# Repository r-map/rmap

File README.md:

Description

software to collect weather data contributed by citizens; to make
these data available for weather services and homeland security; to
provide feedback to the data contributors so that they have the tools
to check and improve their data quality

Stima open source hardware datalogger

RMAP server software

http://doc.rmap.cc

http://rmap.cc

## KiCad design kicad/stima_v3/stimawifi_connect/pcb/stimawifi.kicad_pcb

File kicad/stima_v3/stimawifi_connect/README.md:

# STiMA WiFi Compact pcb base

Kicad project for a compat pcb useful for a portable monitoring station.

Directory tree structure inspired by https://github.com/sdp8483/kicad_dir_structure/tree/master
github repository based on Hackaday article: https://hackaday.com/2017/05/18/kicad-best-practises-library-management/

## Directory structure

 - __./pcb__        Kicad files
 - __./mechanical__ 3d printing related files

 - __./pcb/pcb_render__ Board 3d renderings
 - __./pcb_3d_models__  Kicad 3d models needed for rendering
 - __./pcb/images__  Images for Silk screen
 - __./pcb/lib_fp__   Local Footprints libraries
 - __./pcb/lib_sch__  Local Symbols libraries

## Related project

https://github.com/r-map/rmap

It is a software aimed to 
 - collect air quality data contributed by citizens; 
 - make collected data available for weather services and homeland security; 
 - provide feedback to the data contributors for educational purpose.

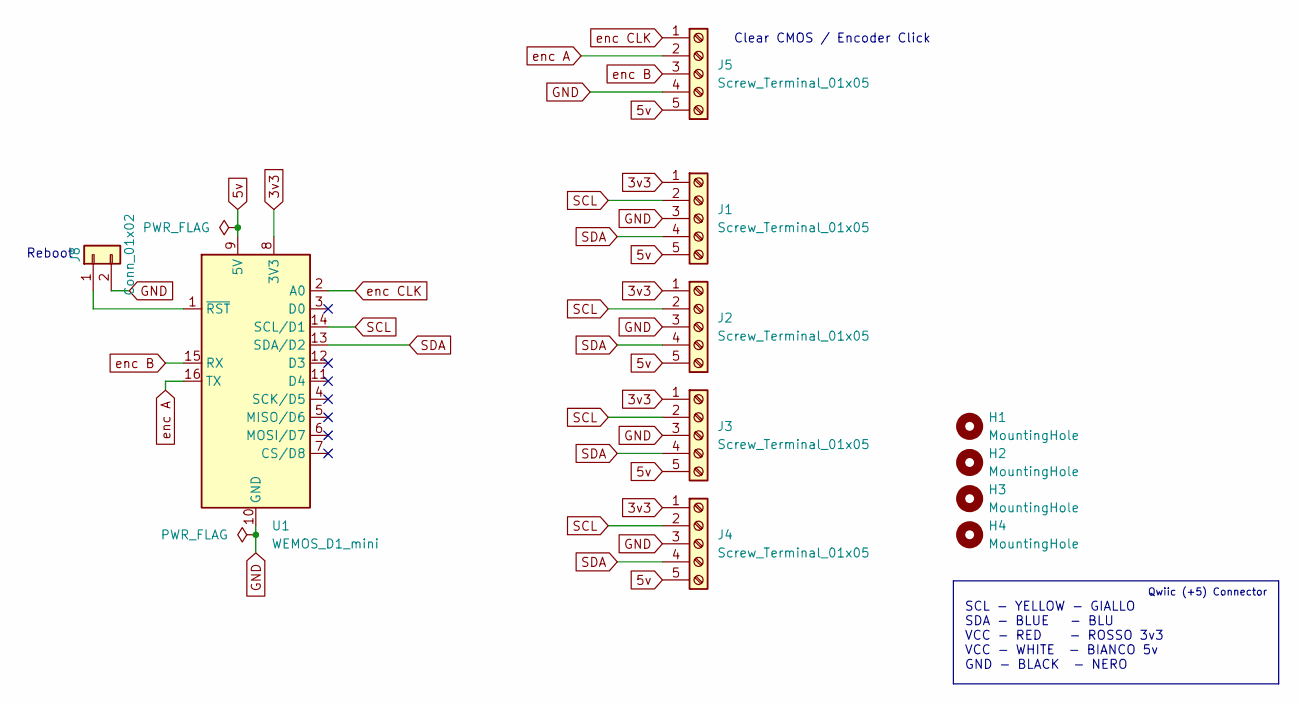
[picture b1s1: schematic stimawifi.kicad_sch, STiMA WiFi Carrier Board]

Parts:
H1, H2, H3, H4: MountingHole; MountingHole_3.2mm_M3
J1, J2, J3, J4, J5: Screw_Terminal_01x05; TerminalBlock_Xinya_XY308-2.54-5P_1x05_P2.54mm_Horizontal
J8: Conn_01x02; PinHeader_1x02_P2.54mm_Vertical
U1: WEMOS_D1_mini; WEMOS_D1_mini_light

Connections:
3v3: J1.1, J2.1, J3.1, J4.1, U1.8 (3V3)
5v: J1.5, J2.5, J3.5, J4.5, J5.5, U1.9 (5V)
GND: J1.3, J2.3, J3.3, J4.3, J5.4, J8.2, U1.10 (GND)
unnamed: J8.1, U1.1 (~RST)
SCL: J1.2, J2.2, J3.2, J4.2, U1.14 (SCL/D1)
SDA: J1.4, J2.4, J3.4, J4.4, U1.13 (SDA/D2)
enc A: J5.2, U1.16 (TX)
enc B: J5.3, U1.15 (RX)
enc CLK: J5.1, U1.2 (A0)

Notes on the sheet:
Clear CMOS / Encoder Click
SCL - YELLOW - GIALLO SDA - BLUE - BLU VCC - RED - ROSSO 3v3 VCC - WHITE - BIANCO 5v GND - BLACK - NERO
Qwiic (+5) Connector
Reboot

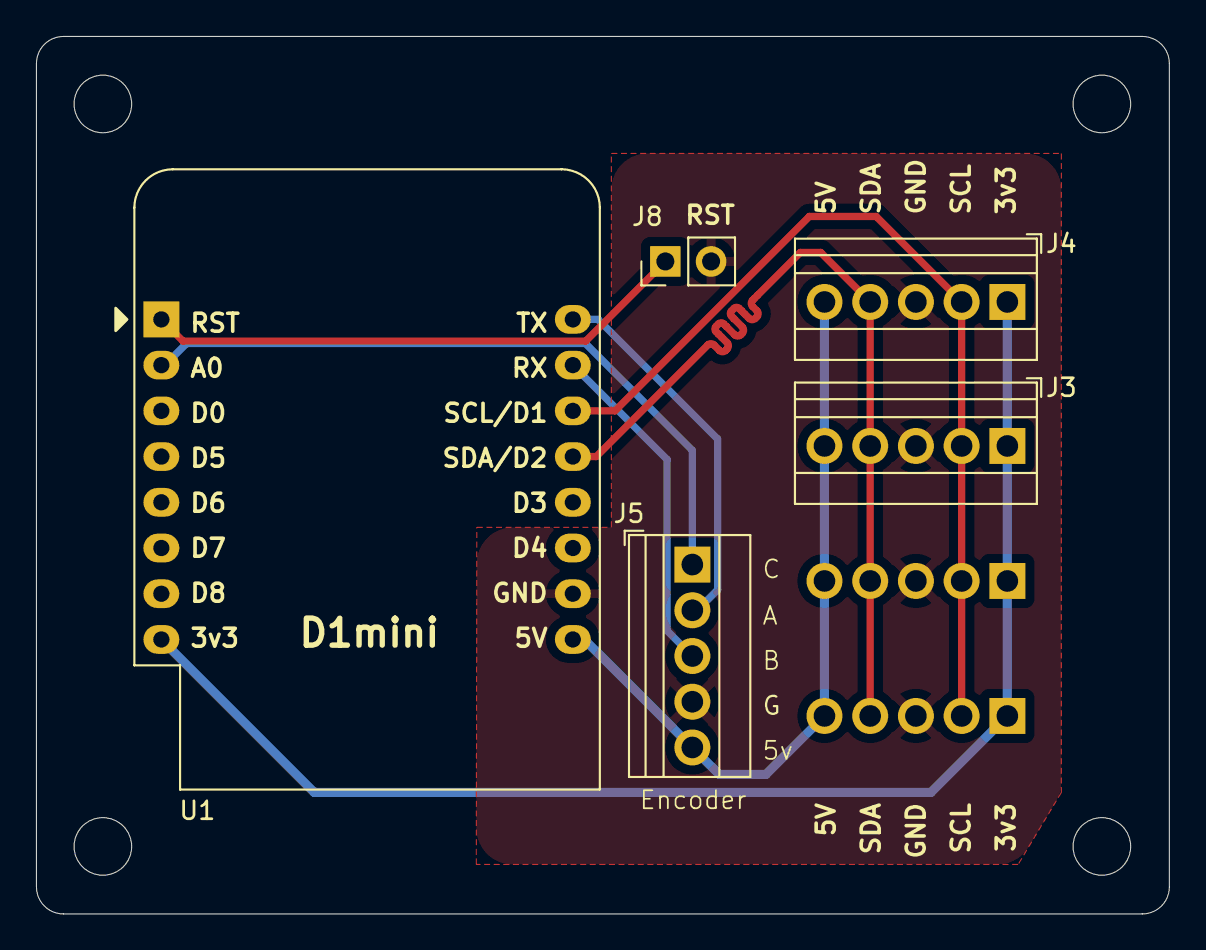
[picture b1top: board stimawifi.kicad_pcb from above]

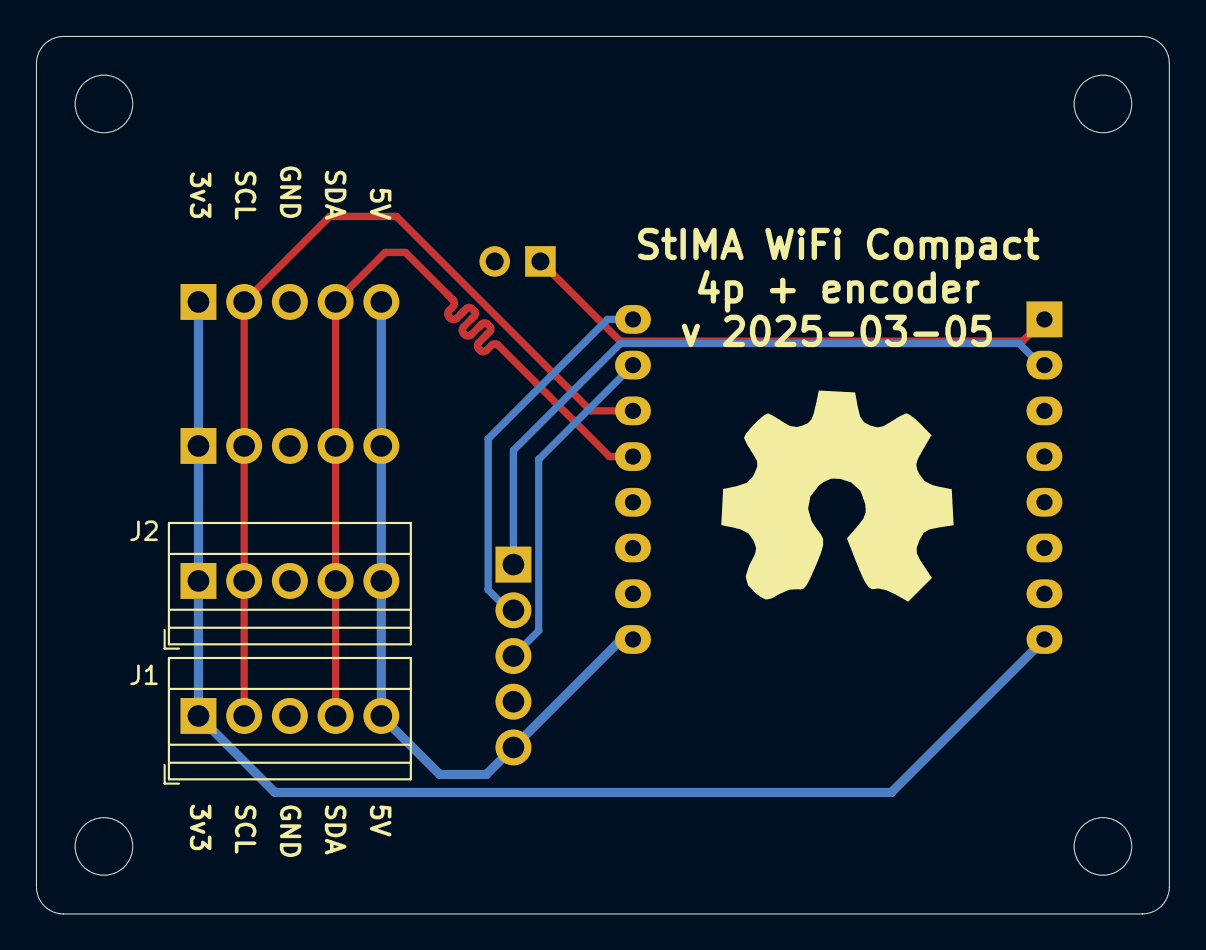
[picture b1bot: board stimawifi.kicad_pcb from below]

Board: 2 copper layers, 62.9 x 48.8 mm, 12 parts (3 on the bottom side), 9 nets.

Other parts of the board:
Open Hardvare Logo: LOGO; ohlogo

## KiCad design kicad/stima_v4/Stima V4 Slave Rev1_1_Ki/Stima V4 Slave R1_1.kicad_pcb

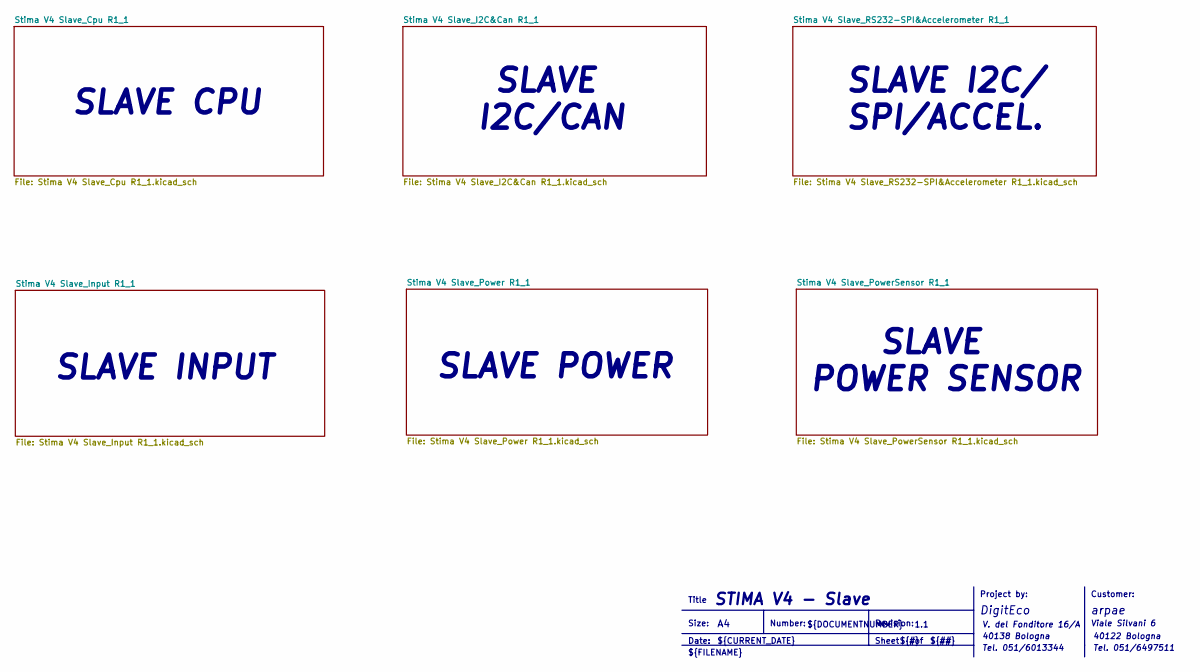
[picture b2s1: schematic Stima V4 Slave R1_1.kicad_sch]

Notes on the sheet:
Tel. 051/6013344
1.1
SLAVE CPU
Project by:
${#}
${TITLE}
${CURRENT_DATE}
Viale Silvani 6
DigitEco
${FILENAME}
SLAVE POWER SENSOR
${##}
${DOCUMENTNUMBER}
STIMA V4 - Slave
Size:
Number:
SLAVE I2C/CAN
Sheet
V. del Fonditore 16/A
Customer:
arpae
40138 Bologna
Date:
Title
Revision:
Tel. 051/6497511
SLAVE POWER
SLAVE INPUT
SLAVE I2C/ SPI/ACCEL.
40122 Bologna

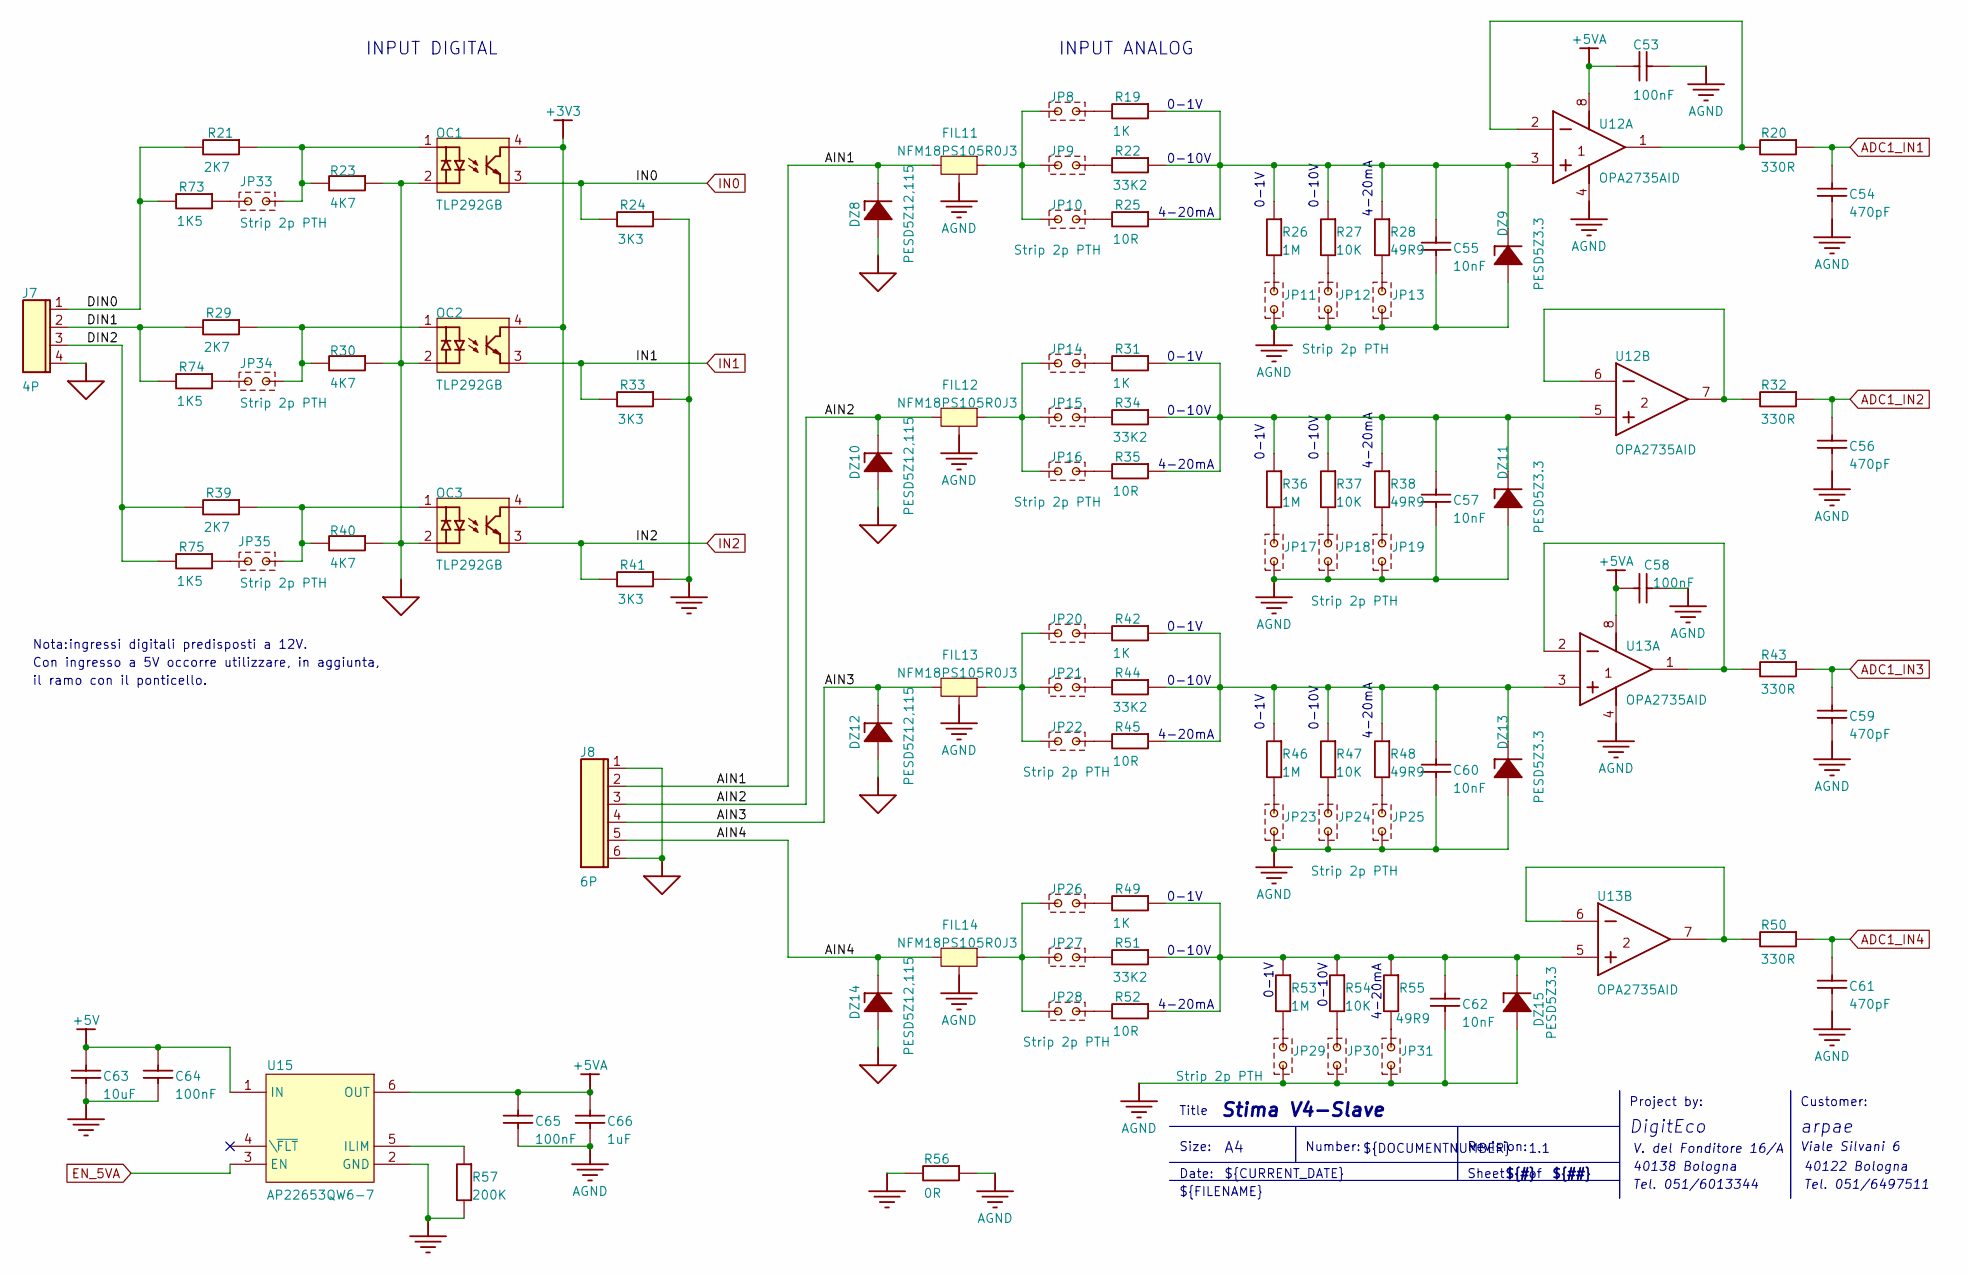
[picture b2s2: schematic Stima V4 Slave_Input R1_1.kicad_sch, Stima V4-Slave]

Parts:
C53, C58, C64, C65: 100nF; 0603; VOLTAGE 50V
C54, C56, C59, C61: 470pF; 0603; VOLTAGE 50V
C55, C57, C60, C62: 10nF; 0603; VOLTAGE 50V
C63: 10uF; 0603; VOLTAGE 20V
C66: 1uF; 0603; VOLTAGE 20V
DZ8, DZ10, DZ12, DZ14: PESD5Z12,115; SOD 523(SC-79)
DZ9, DZ11, DZ13, DZ15: PESD5Z3.3; SOD 523(SC-79)
FIL11, FIL12, FIL13, FIL14: NFM18PS105R0J3; NFM18PS
J7: 4P; CONN_4P-P381
J8: 6P; CONN_6P-P381
JP8, JP9, JP10, JP11, JP12, JP13, JP14, JP15, JP16, JP17, JP18, JP19, JP20, JP21, JP22, JP23, JP24, JP25, JP26, JP27, JP28, JP29, JP30, JP31, JP33, JP34, JP35: Strip 2p PTH; STRIP2P
OC1, OC2, OC3: TLP292GB; SO4-OPTO
R19, R31, R42, R49: 1K; 0603
R20, R32, R43, R50: 330R; 0603
R21, R29, R39: 2K7; 0805
R22, R34, R44, R51: 33K2; 0603
R23, R30, R40: 4K7; 0603
R24, R33, R41: 3K3; 0603
R25, R35, R45, R52: 10R; 0603
R26, R36, R46, R53: 1M; 0603
R27, R37, R47, R54: 10K; 0603
R28, R38, R48, R55: 49R9; 0603
R56: 0R; 0603
R57: 200K; 0603
R73, R74, R75: 1K5; 0805
U12, U13: OPA2735AID; SO8
U15: AP22653QW6-7; SOT26

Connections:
+3V3: OC1.4, OC2.4, OC3.4; also elsewhere on the board
+5V: C63.1, C64.1, U15.1 (IN); also elsewhere on the board
+5VA: C53.1, C58.1, C65.1, C66.1, U12.8 (V+), U13.8 (V+), U15.6 (OUT)
/Stima V4 Slave_Input R1_1/AIN1: DZ8.1 (K), FIL11.1 (I), J8.2
/Stima V4 Slave_Input R1_1/AIN2: DZ10.1 (K), FIL12.1 (I), J8.3
/Stima V4 Slave_Input R1_1/AIN3: DZ12.1 (K), FIL13.1 (I), J8.4
/Stima V4 Slave_Input R1_1/AIN4: DZ14.1 (K), FIL14.1 (I), J8.5
/Stima V4 Slave_Input R1_1/DIN0: J7.1, R21.1, R73.1
/Stima V4 Slave_Input R1_1/DIN1: J7.2, R29.1, R74.1
/Stima V4 Slave_Input R1_1/DIN2: J7.3, R39.1, R75.1
ADC1_IN1: C54.1, R20.2; also elsewhere on the board
ADC1_IN2: C56.1, R32.2; also elsewhere on the board
ADC1_IN3: C59.1, R43.2; also elsewhere on the board
ADC1_IN4: C61.1, R50.2; also elsewhere on the board
AGND: C53.2, C54.2, C55.2, C56.2, C57.2, C58.2, C59.2, C60.2, C61.2, C62.2, C65.2, C66.2, DZ9.2 (A), DZ11.2 (A), DZ13.2 (A), DZ15.2 (A), FIL11.3 (M), FIL12.3 (M), FIL13.3 (M), FIL14.3 (M), JP11.1, JP12.1, JP13.1, JP17.1, JP18.1, JP19.1, JP23.1, JP24.1, JP25.1, JP29.1, JP30.1, JP31.1, R56.2, U12.4 (V-), U13.4 (V-); also elsewhere on the board
EGND: DZ8.2 (A), DZ10.2 (A), DZ12.2 (A), DZ14.2 (A), J7.4, J8.1, J8.6, OC1.2, OC2.2, OC3.2, R23.2, R30.2, R40.2; also elsewhere on the board
EN_5VA: U15.3 (EN); also elsewhere on the board
GND: C63.2, C64.2, R24.2, R33.2, R41.2, R56.1, R57.2, U15.2 (GND); also elsewhere on the board
IN0: OC1.3, R24.1; also elsewhere on the board
IN1: OC2.3, R33.1; also elsewhere on the board
IN2: OC3.3, R41.1; also elsewhere on the board
unnamed: C55.1, DZ9.1 (K), R19.2, R22.2, R25.2, R26.2, R27.2, R28.2, U12.3 (IN+)
unnamed: C57.1, DZ11.1 (K), R31.2, R34.2, R35.2, R36.2, R37.2, R38.2, U12.5 (IN+)
unnamed: C60.1, DZ13.1 (K), R42.2, R44.2, R45.2, R46.2, R47.2, R48.2, U13.3 (IN+)
unnamed: C62.1, DZ15.1 (K), R49.2, R51.2, R52.2, R53.2, R54.2, R55.2, U13.5 (IN+)
unnamed: FIL11.2 (O), JP8.1, JP9.1, JP10.1
unnamed: FIL12.2 (O), JP14.1, JP15.1, JP16.1
unnamed: FIL13.2 (O), JP20.1, JP21.1, JP22.1
unnamed: FIL14.2 (O), JP26.1, JP27.1, JP28.1
unnamed: JP8.2, R19.1
unnamed: JP9.2, R22.1
unnamed: JP10.2, R25.1
unnamed: JP11.2, R26.1
unnamed: JP12.2, R27.1
unnamed: JP13.2, R28.1
unnamed: JP14.2, R31.1
unnamed: JP15.2, R34.1
unnamed: JP16.2, R35.1
unnamed: JP17.2, R36.1
unnamed: JP18.2, R37.1
unnamed: JP19.2, R38.1
unnamed: JP20.2, R42.1
unnamed: JP21.2, R44.1
unnamed: JP22.2, R45.1
unnamed: JP23.2, R46.1
unnamed: JP24.2, R47.1
unnamed: JP25.2, R48.1
unnamed: JP26.2, R49.1
unnamed: JP27.2, R51.1
unnamed: JP28.2, R52.1
unnamed: JP29.2, R53.1
unnamed: JP30.2, R54.1
unnamed: JP31.2, R55.1
unnamed: JP33.1, R73.2
unnamed: JP33.2, OC1.1, R21.2, R23.1
unnamed: JP34.1, R74.2
unnamed: JP34.2, OC2.1, R29.2, R30.1
unnamed: JP35.1, R75.2
unnamed: JP35.2, OC3.1, R39.2, R40.1
unnamed: R20.1, U12.1 (OUT), U12.2 (IN-)
unnamed: R32.1, U12.6 (IN-), U12.7 (OUT)
unnamed: R43.1, U13.1 (OUT), U13.2 (IN-)
unnamed: R50.1, U13.6 (IN-), U13.7 (OUT)
unnamed: R57.1, U15.5 (ILIM)

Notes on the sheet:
INPUT DIGITAL
0-1V
${FILENAME}
ingressi digitali predisposti a 12V.
Title
arpae
Tel. 051/6013344
0-10V
${TITLE}
Number:
Sheet
Viale Silvani 6
40138 Bologna
4-20mA
il ramo con il ponticello.
Customer:
${CURRENT_DATE}
40122 Bologna
Tel. 051/6497511
Date:
Size:
${#}
INPUT ANALOG
1.1
${##}
Nota:
Revision:
DigitEco
${DOCUMENTNUMBER}
V. del Fonditore 16/A
Con ingresso a 5V occorre utilizzare, in aggiunta,
Project by:

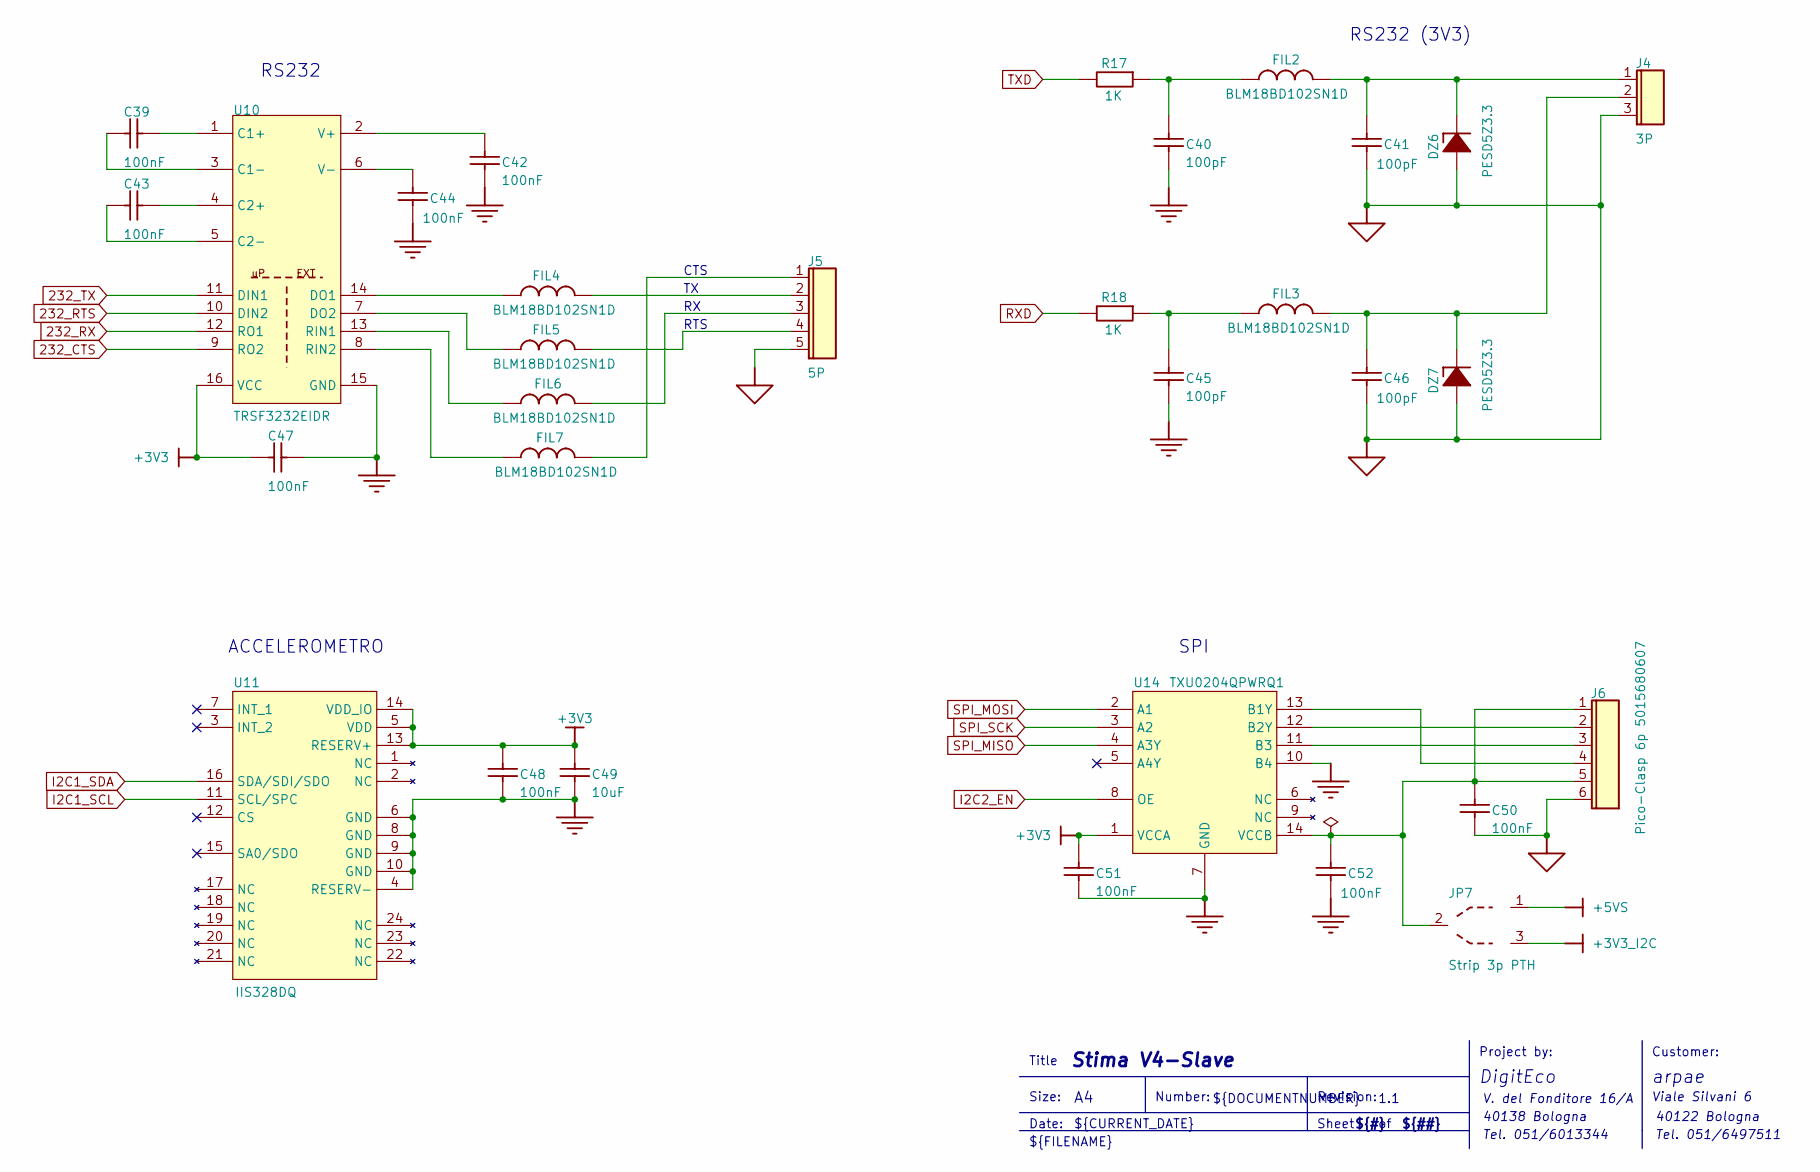
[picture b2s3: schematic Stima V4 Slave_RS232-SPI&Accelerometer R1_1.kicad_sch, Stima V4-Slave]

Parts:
C39, C42, C43, C44, C47, C48, C50, C51, C52: 100nF; 0603; VOLTAGE 50V
C40, C41, C45, C46: 100pF; 0603; VOLTAGE 50V
C49: 10uF; 0603; VOLTAGE 16V
DZ6, DZ7: PESD5Z3.3; SOD 523(SC-79)
FIL2, FIL3, FIL4, FIL5, FIL6, FIL7: BLM18BD102SN1D; 0603
J4: 3P; CONN_3P-P381
J5: 5P; CONN_5P-P381
J6: Pico-Clasp 6p 5015680607; PICOCLASP6P_REV-MIO
JP7: Strip 3p PTH; STRIP3PP254
R17, R18: 1K; 0603
U10: TRSF3232EIDR; SO16
U11: IIS328DQ; VQFN24
U14: TXU0204QPWRQ1; TSSOP14

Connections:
232_CTS: U10.9 (RO2); also elsewhere on the board
232_RTS: U10.10 (DIN2); also elsewhere on the board
232_RX: U10.12 (RO1); also elsewhere on the board
232_TX: U10.11 (DIN1); also elsewhere on the board
+3V3: C47.1, C48.1, C49.1, C51.1, U10.16 (VCC), U11.5 (VDD), U11.13 (RESERV+), U11.14 (VDD_IO), U14.1 (VCCA); also elsewhere on the board
+3V3_I2C: JP7.3; also elsewhere on the board
+5VS: JP7.1; also elsewhere on the board
EGND: C41.1, C46.1, C50.2, DZ6.2 (A), DZ7.2 (A), J4.3, J5.5, J6.6; also elsewhere on the board
GND: C40.1, C42.1, C44.1, C45.1, C47.2, C48.2, C49.2, C51.2, C52.2, U10.15 (GND), U11.4 (RESERV-), U11.6 (GND), U11.8 (GND), U11.9 (GND), U11.10 (GND), U14.7 (GND), U14.10 (B4); also elsewhere on the board
I2C1_SCL: U11.11 (SCL/SPC); also elsewhere on the board
I2C1_SDA: U11.16 (SDA/SDI/SDO); also elsewhere on the board
I2C2_EN: U14.8 (OE); also elsewhere on the board
unnamed: C40.2, FIL2.1, R17.2
unnamed: C45.2, FIL3.1, R18.2
unnamed: C41.2, DZ6.1 (K), FIL2.2, J4.1
unnamed: C46.2, DZ7.1 (K), FIL3.2, J4.2
unnamed: FIL4.2, J5.2
unnamed: FIL5.2, J5.4
unnamed: FIL6.2, J5.3
unnamed: FIL7.2, J5.1
unnamed: C39.2, U10.1 (C1+)
unnamed: C39.1, U10.3 (C1-)
unnamed: C43.2, U10.4 (C2+)
unnamed: C43.1, U10.5 (C2-)
unnamed: FIL4.1, U10.14 (DO1)
unnamed: FIL5.1, U10.7 (DO2)
unnamed: FIL6.1, U10.13 (RIN1)
unnamed: FIL7.1, U10.8 (RIN2)
unnamed: C42.2, U10.2 (V+)
unnamed: C44.2, U10.6 (V-)
unnamed: J6.4, U14.13 (B1Y)
unnamed: J6.2, U14.12 (B2Y)
unnamed: J6.3, U14.11 (B3)
unnamed: C50.1, C52.1, J6.1, J6.5, JP7.2, U14.14 (VCCB)
RXD: R18.1; also elsewhere on the board
SPI_MISO: U14.4 (A3Y); also elsewhere on the board
SPI_MOSI: U14.2 (A1); also elsewhere on the board
SPI_SCK: U14.3 (A2); also elsewhere on the board
TXD: R17.1; also elsewhere on the board

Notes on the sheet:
ACCELEROMETRO
V. del Fonditore 16/A
${CURRENT_DATE}
RTS
Sheet
Revision:
${TITLE}
RS232 (3V3)
Customer:
arpae
Viale Silvani 6
40122 Bologna
${#}
Tel. 051/6497511
Date:
1.1
CTS
RS232
${##}
Number:
${DOCUMENTNUMBER}
40138 Bologna
${FILENAME}
Size:
Project by:
Title
Tel. 051/6013344
SPI
DigitEco

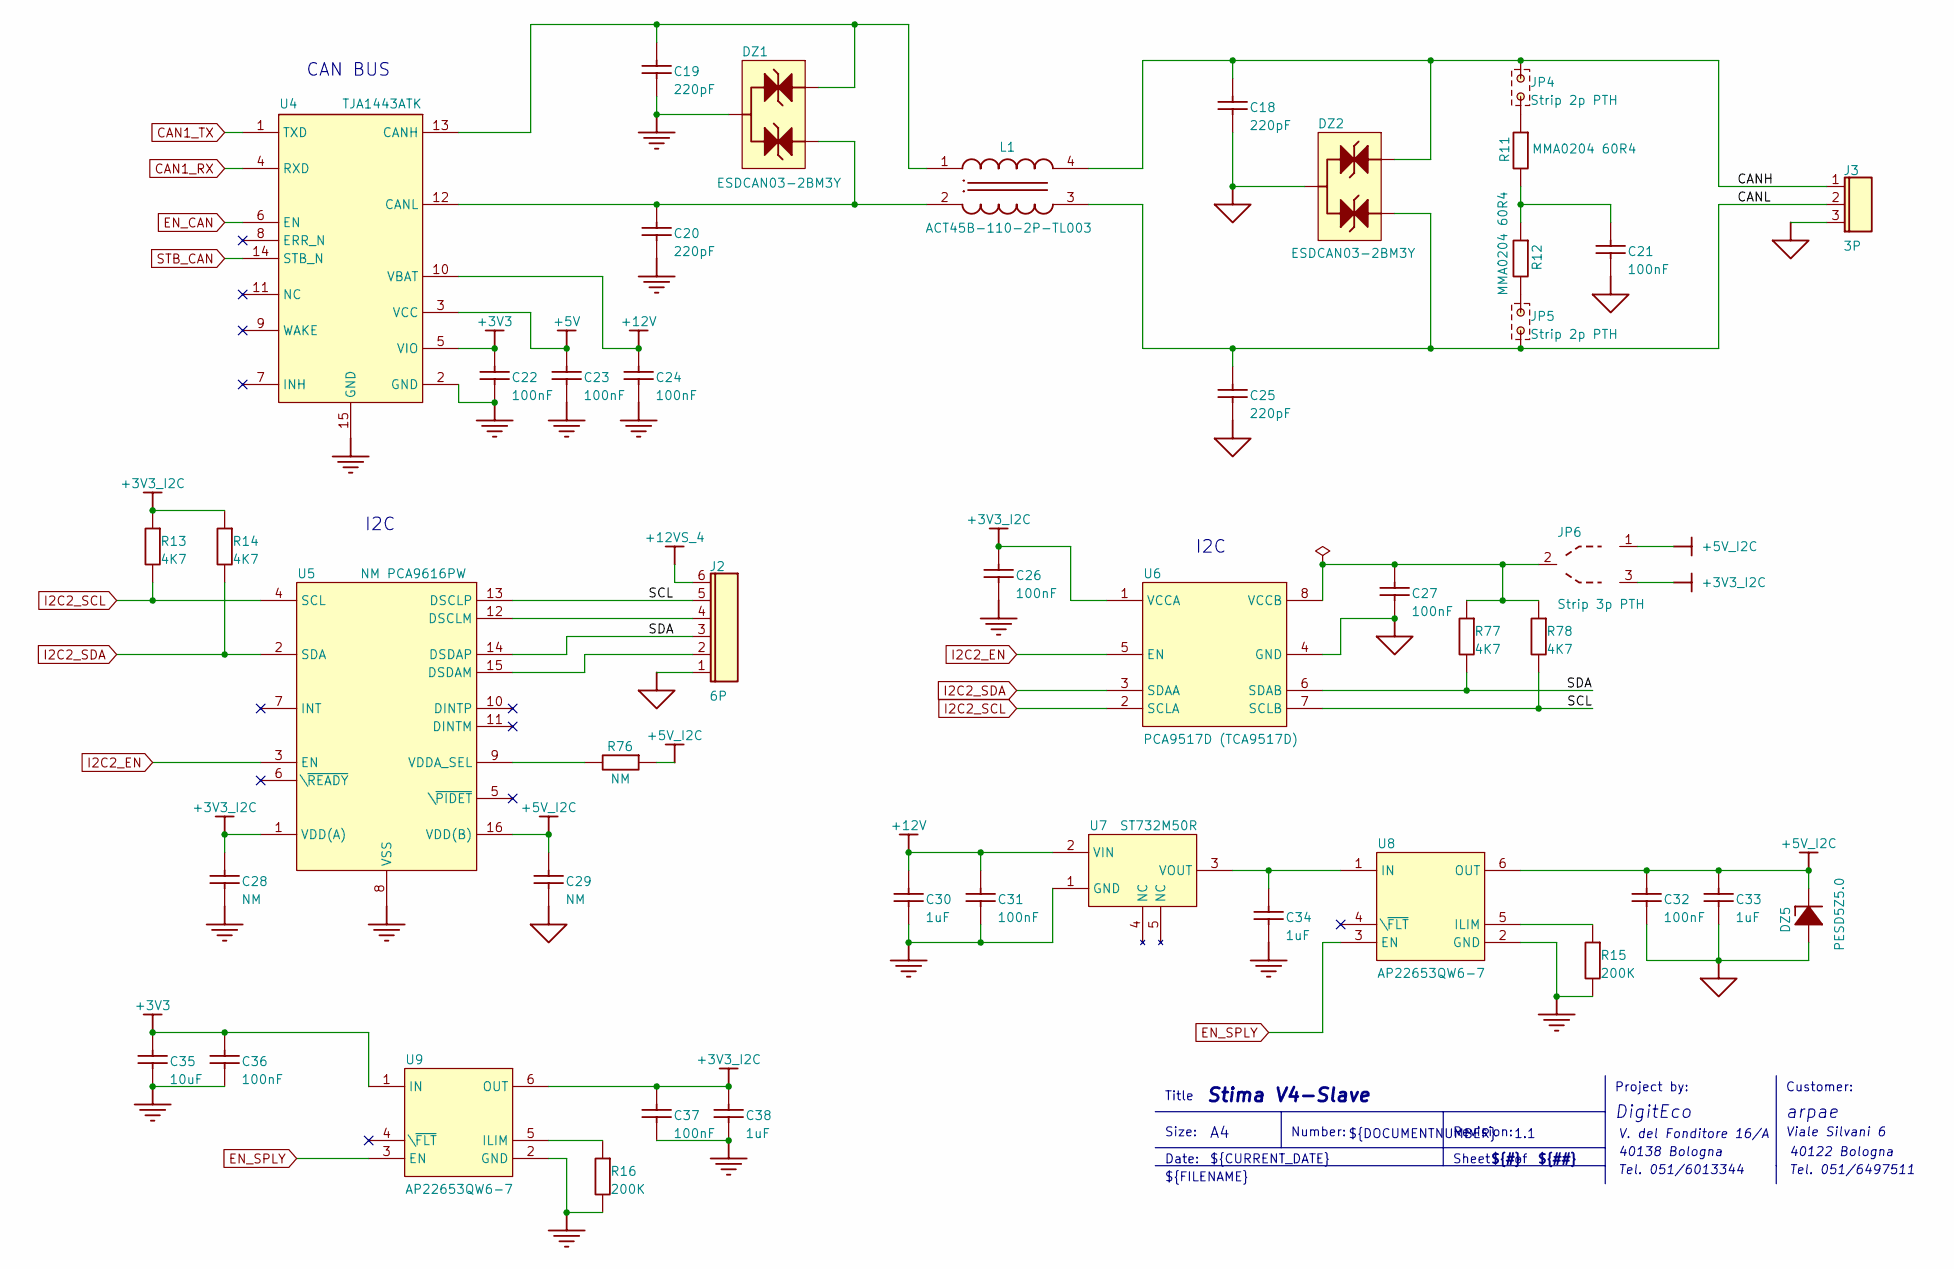
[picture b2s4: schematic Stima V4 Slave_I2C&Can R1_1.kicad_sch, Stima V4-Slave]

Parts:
C18, C19, C20, C25: 220pF; 0603; VOLTAGE 50V
C21, C22, C23, C24, C26, C27, C31, C32, C36, C37: 100nF; 0603; VOLTAGE 50V
C28, C29: NM; 0603; VOLTAGE 50V
C30, C33, C34, C38: 1uF; 0603; VOLTAGE 20V
C35: 10uF; 0603; VOLTAGE 20V
DZ1, DZ2: ESDCAN03-2BM3Y; QFN-3L-DFN1110
DZ5: PESD5Z5.0; SOD 523(SC-79)
J2: 6P; CONN_6P-P381
J3: 3P; CONN_3P-P381
JP4, JP5: Strip 2p PTH; STRIP2P
JP6: Strip 3p PTH; STRIP3PP254
L1: ACT45B-110-2P-TL003; ACT45B TDK-MIO
R11, R12: MMA0204 60R4; MELFRESMMA0204
R13, R14, R77, R78: 4K7; 0603
R15, R16: 200K; 0603
R76: NM; 0603
U4: TJA1443ATK; HVSON14
U5: NM PCA9616PW; TSSOP16
U6: PCA9517D (TCA9517D); SO8
U7: ST732M50R; SOT23_5
U8, U9: AP22653QW6-7; SOT26

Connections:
+3V3: C22.1, C35.1, C36.1, U4.5 (VIO), U9.1 (IN); also elsewhere on the board
+3V3_I2C: C26.1, C28.1, C37.1, C38.1, JP6.3, R13.2, R14.2, U5.1 (VDD(A)), U6.1 (VCCA), U9.6 (OUT); also elsewhere on the board
+5V: C23.1, U4.3 (VCC); also elsewhere on the board
+5V_I2C: C29.1, C32.1, C33.1, DZ5.1 (K), JP6.1, R76.1, U5.16 (VDD(B)), U8.6 (OUT)
+12V: C24.2, C30.1, C31.1, U4.10 (VBAT), U7.2 (VIN); also elsewhere on the board
+12VS_4: J2.6; also elsewhere on the board
/Stima V4 Slave_I2C&Can R1_1/CANH: C18.2, DZ2.1 (A/K), J3.1, JP4.1, L1.4
/Stima V4 Slave_I2C&Can R1_1/CANL: C25.2, DZ2.2 (A/K), J3.2, JP5.2, L1.3
/Stima V4 Slave_I2C&Can R1_1/SCL: J2.5, R78.1, U5.13 (DSCLP), U6.7 (SCLB)
/Stima V4 Slave_I2C&Can R1_1/SDA: J2.3, R77.1, U5.14 (DSDAP), U6.6 (SDAB)
CAN1_RX: U4.4 (RXD); also elsewhere on the board
CAN1_TX: U4.1 (TXD); also elsewhere on the board
EGND: C18.1, C21.1, C25.1, C27.2, C29.2, C32.2, C33.2, DZ2.3 (A/K), DZ5.2 (A), J2.1, J3.3, U6.4 (GND); also elsewhere on the board
EN_CAN: U4.6 (EN); also elsewhere on the board
EN_SPLY: U8.3 (EN), U9.3 (EN); also elsewhere on the board
GND: C19.1, C20.1, C22.2, C23.2, C24.1, C26.2, C28.2, C30.2, C31.2, C34.2, C35.2, C36.2, C37.2, C38.2, DZ1.3 (A/K), R15.2, R16.2, U4.2 (GND), U4.15 (GND), U5.8 (VSS), U7.1 (GND), U8.2 (GND), U9.2 (GND); also elsewhere on the board
I2C2_EN: U5.3 (EN), U6.5 (EN); also elsewhere on the board
I2C2_SCL: R13.1, U5.4 (SCL), U6.2 (SCLA); also elsewhere on the board
I2C2_SDA: R14.1, U5.2 (SDA), U6.3 (SDAA); also elsewhere on the board
unnamed: C21.2, R11.1, R12.2
unnamed: JP4.2, R11.2
unnamed: JP5.1, R12.1
unnamed: C19.2, DZ1.2 (A/K), L1.1, U4.13 (CANH)
unnamed: C20.2, DZ1.1 (A/K), L1.2, U4.12 (CANL)
unnamed: J2.4, U5.12 (DSCLM)
unnamed: J2.2, U5.15 (DSDAM)
unnamed: R76.2, U5.9 (VDDA_SEL)
unnamed: C27.1, JP6.2, R77.2, R78.2, U6.8 (VCCB)
unnamed: C34.1, U7.3 (VOUT), U8.1 (IN)
unnamed: R15.1, U8.5 (ILIM)
unnamed: R16.1, U9.5 (ILIM)
STB_CAN: U4.14 (STB_N); also elsewhere on the board

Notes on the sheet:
Size:
40122 Bologna
Number:
Customer:
${FILENAME}
Tel. 051/6013344
40138 Bologna
CAN BUS
${TITLE}
arpae
Date:
I2C
${##}
1.1
V. del Fonditore 16/A
Project by:
Revision:
Title
Viale Silvani 6
Sheet
${#}
Tel. 051/6497511
DigitEco
${CURRENT_DATE}
${DOCUMENTNUMBER}

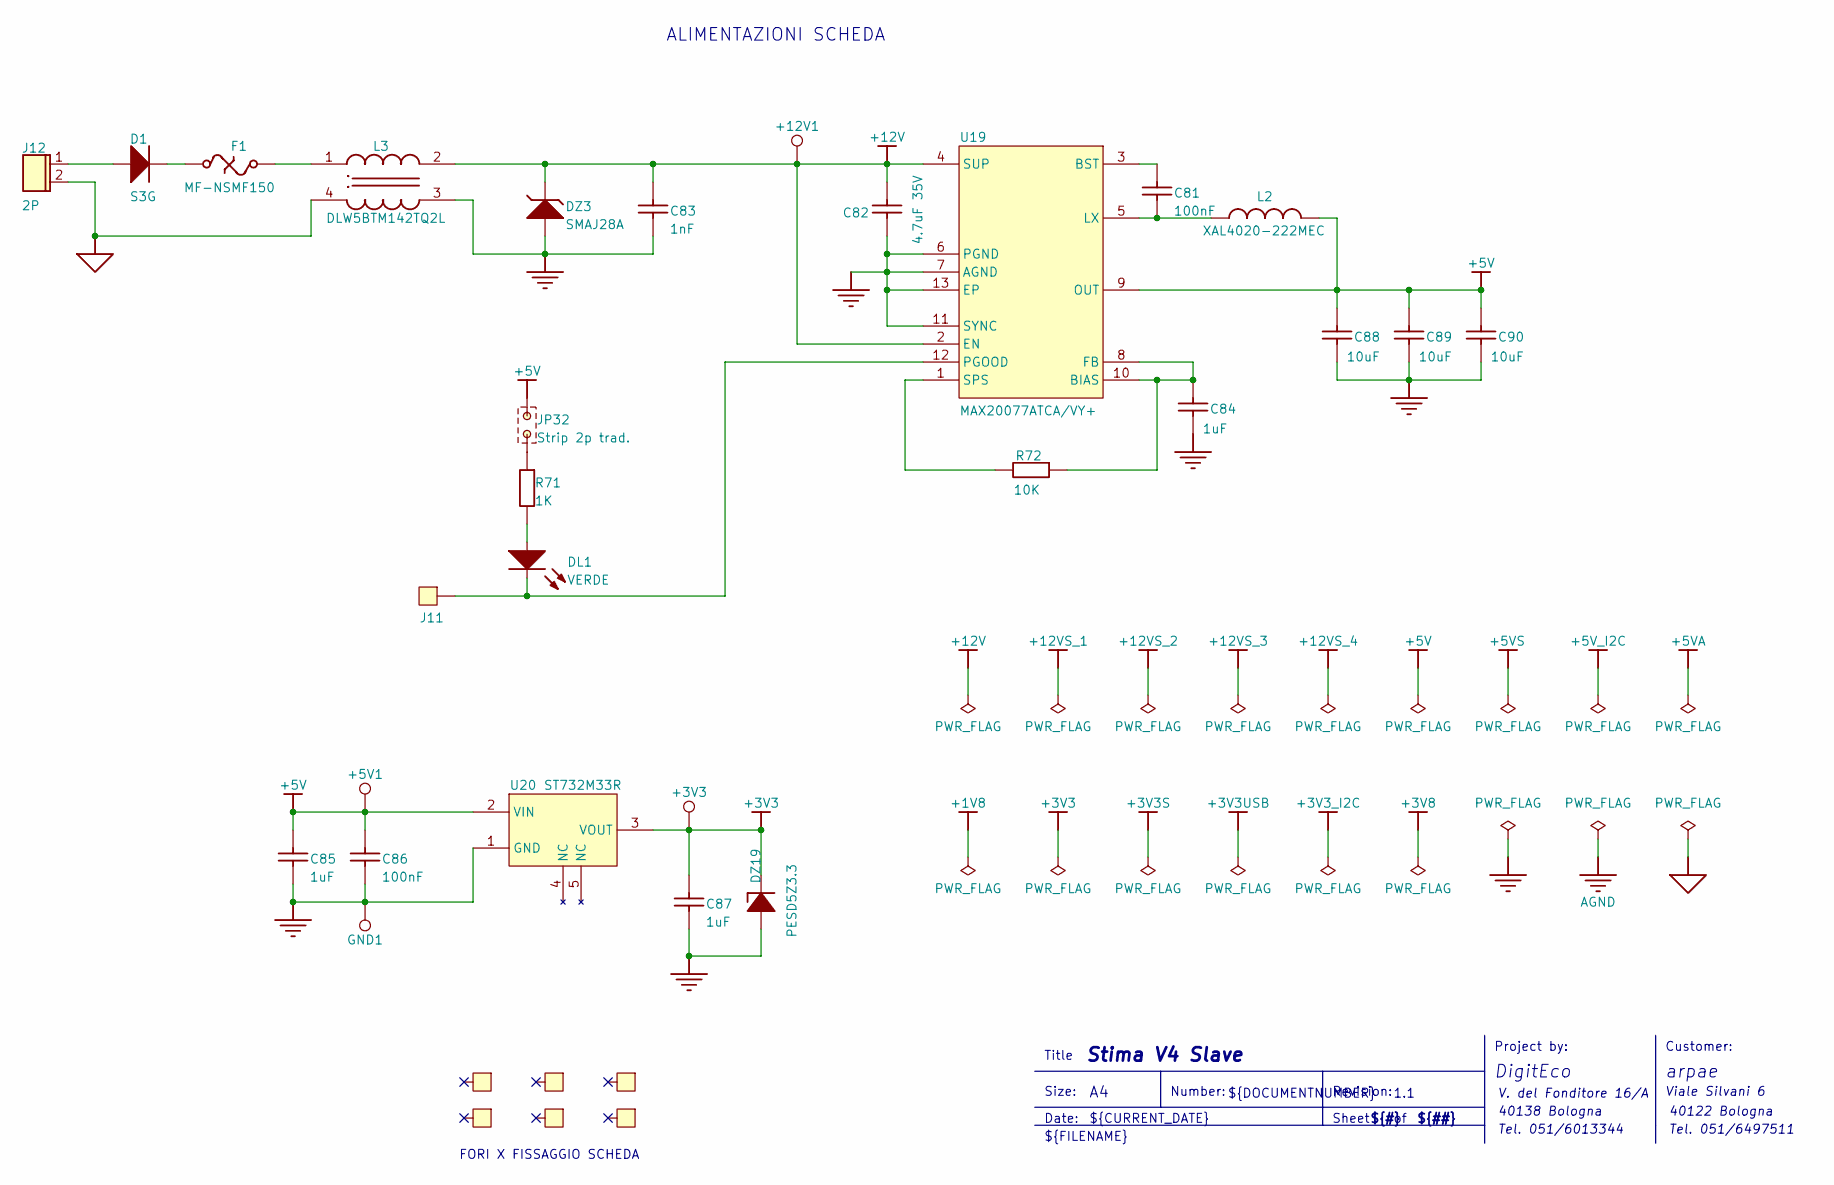
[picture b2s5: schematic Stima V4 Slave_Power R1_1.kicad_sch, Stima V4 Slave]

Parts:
+3V3, +5V1, +12V1: TestPoint; TP
A1, A2, A3, A4, A5, A6: ViteDado; ViteDado4
C81: 100nF; 0805; VOLTAGE 50V
C82: 4.7uF 35V; 1206; VOLTAGE 35V
C83: 1nF; 0603; VOLTAGE 50V
C84, C85, C87: 1uF; 0603; VOLTAGE 20V
C86: 100nF; 0603; VOLTAGE 50V
C88, C89, C90: 10uF; 0603; VOLTAGE 20V
D1: S3G; DO-214AB
DL1: VERDE; 0805-led
DZ3: SMAJ28A; SMA
DZ19: PESD5Z3.3; SOD 523(SC-79)
F1: MF-NSMF150; 1206
GND1: TestPoint; TP
J11: VIAS1; VIAS0_8
J12: 2P; CONN_2P-P381
JP32: Strip 2p trad.; STRIP2P
L2: XAL4020-222MEC; COIL COILCRAFT XAL4020-MIO
L3: DLW5BTM142TQ2L; FILTRO DLW5B
R71: 1K; 0805
R72: 10K; 0603
U19: MAX20077ATCA/VY+; TDFN 12L
U20: ST732M33R; SOT23_5

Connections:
+3V3: +3V3.1, C87.1, DZ19.1 (K), U20.3 (VOUT); also elsewhere on the board
+5V: +5V1.1, C85.1, C86.1, C88.2, C89.2, C90.2, JP32.1, L2.2, U19.9 (OUT), U20.2 (VIN); also elsewhere on the board
+12V: +12V1.1, C82.1, C83.1, DZ3.1 (K), L3.2, U19.2 (EN), U19.4 (SUP); also elsewhere on the board
EGND: J12.2, L3.4; also elsewhere on the board
GND: C82.2, C83.2, C84.1, C85.2, C86.2, C87.2, C88.1, C89.1, C90.1, DZ3.2 (A), DZ19.2 (A), GND1.1, L3.3, U19.6 (PGND), U19.7 (AGND), U19.11 (SYNC), U19.13 (EP), U20.1 (GND); also elsewhere on the board
unnamed: D1.2 (A), J12.1
unnamed: D1.1 (K), F1.1
unnamed: DL1.2 (A), R71.1
unnamed: DL1.1 (K), J11.1, U19.12 (PGOOD)
unnamed: F1.2, L3.1
unnamed: JP32.2, R71.2
unnamed: C84.2, R72.2, U19.8 (FB), U19.10 (BIAS)
unnamed: C81.1, U19.3 (BST)
unnamed: C81.2, L2.1, U19.5 (LX)
unnamed: R72.1, U19.1 (SPS)

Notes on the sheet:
Customer:
${CURRENT_DATE}
ALIMENTAZIONI SCHEDA
V. del Fonditore 16/A
1.1
DigitEco
Date:
40138 Bologna
FORI X FISSAGGIO SCHEDA
Number:
Size:
Tel. 051/6497511
Viale Silvani 6
${FILENAME}
${DOCUMENTNUMBER}
Sheet
${#}
arpae
${TITLE}
${##}
Project by:
40122 Bologna
Title
Tel. 051/6013344
Revision:

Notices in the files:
kicad/stima_v2/i2c_minid1_base/i2c_minid1_base.kicad_sch:
Licensed as CERN-OHL-P (see LICENSE.readme File)
